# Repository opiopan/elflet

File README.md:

elflet
====

elflet is a home IoT controller based on [ESP-WROOM-32](https://www.espressif.com/en/products/hardware/modules) (ESP32). <br>
Both of hardware designe and firmware code are open source licenced. 
You are free to use any outcome from this project. And you are also free to modify hardware design and firmware code.<br>
elflet will join your home net work with WiFi.
Then elflet can controll home electronic devices through IR remote controll protocol or Bluetooth LE. 
And this device can be behave as sensor node such as temperature sensor.<br>
Unlike other similar products, elflet highly abstructs IR remote controll protocol. Therefore host-side software to collaborate with elflet is very easy to implement.

## Features

* **IR receiver**<br>
Receivd IR remote controller signal is analized such as following abstracted protocol data.

    ```json
    {
        "Protocol": "AEHA",
        "BitCount": 160,
        "Data": "11da270002000000000300001000000000000027"
    }
    ```
    Analized protocol data can be retrieved via 
    [REST interface](docs/REST.md), 
    or can be publishd via MQTT protocol.<br>
    **NOTE:** Supported protocols are NEC, SONY, and AEHA.

* **IR transmitter**<br> 
You can transmit IR remote controller signal by specifying the above level abstracted represatation.<br>
elflet supports two protocols for IR transmitter, 
The first one is 
[REST](docs/REST.md)
, and the other one is original binary protocol.
Regarding this binary protocol, please refer 
[these host-side library codes (`irslib.h`, `irslib.c`)](hosttool).

* **Device Shadow**<br>
Device shadow is designed to help complecated IR command device management such as air conditioner.<br>
elflet analize IR command code pattern according to registered shadow definition, then reflect device status to shadow representation managed in elflet. Following JSON data is a example of shadow status representation.
    ```json
    {
        "NodeName": "elflet-living", 
        "ShadowName": "ac",
        "IsOn": true,
        "Attributes":{
            "Mode": "Cooler",
            "Temperature": 26.5,
            "Humidity": 50
        }
    }
    ```

    Shadow status can be refered via 
    [REST interface](docs/REST.md), and status change of shadow device can be known immediately as publicshed data via MQTT.<br>
    You can also change shadow's status by sending the above format data to elflet via 
    [REST interface](docs/REST.md). 
    In this case, elflet synthesize IR code acording to shadow definition then transmit that.<br>
    A couple of shadow definition examples are shown at
    [here](examples).

* **BLE Keyboard Emulator**<br>
elflet can behave as Bluetooth LE (BLE) keyboard. You can send any key code to a device paired with elflet via Bluetooth LE.<br>
The typical use case of this function is to wake up a PC or server which does not accept WOL packet.

* **Environment Sensor**<br>
Following sensors are installed on elflet.
    * temperature sensor
    * humidity sensor
    * atmospheric pressure sensor
    * luminocity sensors

    You can retrieve sensor values via
    [REST interface](docs/REST.md),
    and can also receive them periodically as MQTT published message.<br>
    elflet supports a SENSOR-ONLY mode to avoid own heat affecting to measuring temperature. In this mode, elflet stays in deep sleep status except when sensor values is captured and they are published.
    You can transit elflet to SENSOR-ONLY mode by using
    [host tool](hosttool).

## PCB
PCB of elfet is designed by using [AUTODESK EAGLE](http://eagle.autodesk.com).
* PCB design files are placed [here](pcb/mainboard)
* You can also use [this gerver data](https://raw.githubusercontent.com/wiki/opiopan/elflet/pcb/elflet-mainboard.zip)
for production
* BOM list is [here](pcb/elflet-bom.xlsx?raw=true)

## Building Firmware
Firmware source codes are placed at 
[here](firmware).
To build firmware binary, please refer 
[this document](firmware/README.md).

## Inital Firmware Downloading
Once elflet firmware runs on elflet board, you can download firmware binary via WiFi (OTA updating). However, you need to download firmware via UART at first time since OTA updating function does not work yet.<br>
Folowing four binary files must be download at correct address in ESP-WROOM-32's SPI flash.

|file to download                        | adress  |
|:---------------------------------------|--------:|
| firmware/buld/bootloader/bootloader.bin|   0x1000|
| firmware/buld/partitions.bin           |   0x8000|
| firmware/build/ota_data_initial.bin    |   0xd000|
| firmware/buld/elflet.bin               |  0x10000|
| firmware/buld/spiffsimage.bin          | 0x3f0000|

elflet exports sevelal ESP32 pins to service port as below. You can download firmware by connection your USB serial dongle to there.

Another way to download firmware is using 
[this jig board](https://raw.githubusercontent.com/wiki/opiopan/elflet/pcb/elflet-jig.zip)
and Raspberry Pi. 
[These tools running on Raspberry Pi](raspitools)
may help you to download or debug elflet firmware.<br>
When use this jig board, please connect following direction.

## Configuration
When initial firmware downloading finish, LED on elflet starts to blink orange. In this state, elflet is working as WiFi access point and it provides Web based setup widzard interface.<br>
The SSID is same as node name of elflet, 
and the initial node name is "`elflet-000000`". Passphrase to connect elflet WiFi access point is same as administorator password, and the initial password is "`elflet00`".
Please connect to elflet WiFi access point by specifing these SSID and passphrase<br>

Once you connect to elflet WiFi access point, you can access to setup widzard. <br>
Since this wizard behaves as same mechanism of [captive portal](https://en.wikipedia.org/wiki/Captive_portal), typical OS shows that wizard window automatically when you connect to elflet WiFi access point.<br>
If no wizard window is shown, try a URL "```http://elflet.setup/```"

**NOTE:** Initial node name and initial administorator password can be change in step of building firmware. Please refer
[this document](firmware/README.md)
regarding the detail. 

By this wizard, you can configure following items:

* WiFi SSID and passphrase to connect
* elflet node name
* administorator password

When the wizard is completed, elflet restarts and LED start to blink white.
After that, elflet connect to your home network if configuration is correct, and LED turns off.<br>
If WiFi configuration is not correct and elflet cannot connect to your home network in 30 seconds, elflet will fall back to CONFIGURATION mode.
In this case, the LED start to blink orange again and you can access setup Wizard.

During elflet is connecting to your home network, setup widzard is not available. If you want to access setup wizard, please transit elflet to CONFIGURATION mode. You can proceed this transition by pressing a button till LED start to blink orange.

To change other detail configuration, please use a host tools, "`elflet-config`" and "`elflet-shadow`". Usage of these tools are described in [this document](hosttool/README.md).

## Licencing

elflet is released under dual open source licence.<br>
[The elfle firmware](firmware)
is in accordance with 
[GNU General Public License, version 2](https://www.gnu.org/licenses/old-licenses/gpl-2.0.en.html).
The other program source files, PCB design, and all documents are coverd by
[Apache License 2.0](http://www.apache.org/licenses/LICENSE-2.0).

## Application Example
My another project [Wakeserver](https://github.com/opiopan/wakeserver) is a good example of elfelt's application.

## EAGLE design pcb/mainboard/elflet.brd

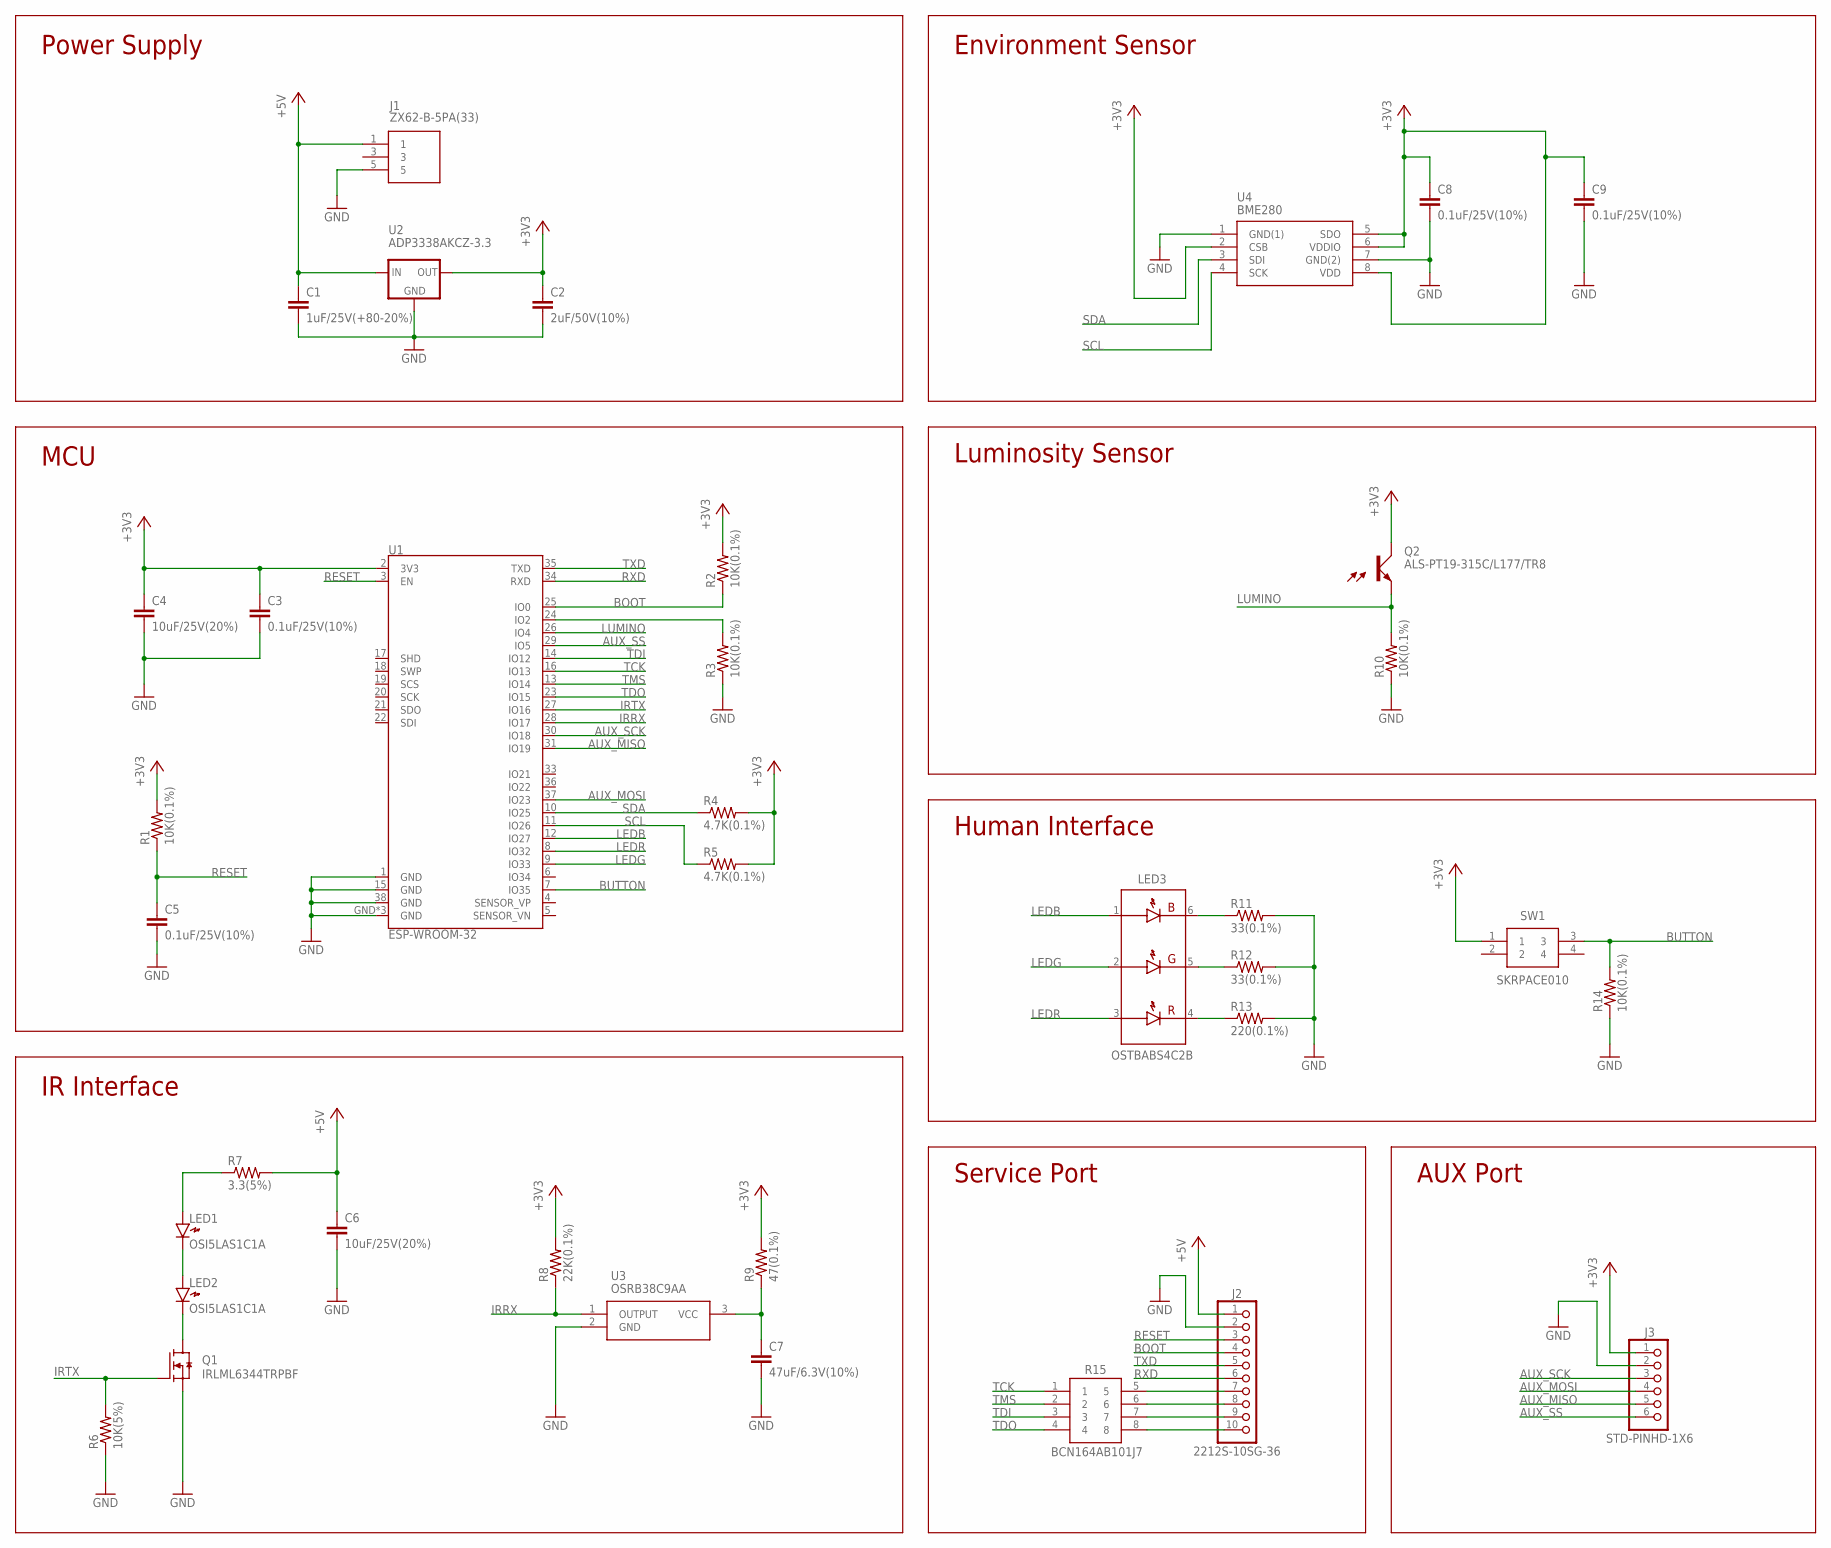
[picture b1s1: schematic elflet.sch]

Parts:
C1: 1uF/25V(+80-20%); C3216
C2: 2uF/50V(10%); C3216
C3, C5, C8, C9: 0.1uF/25V(10%); C1608
C4, C6: 10uF/25V(20%); C1608
C7: 47uF/6.3V(10%); C3216
J1: ZX62-B-5PA(33); ZX62-B-5PA(33)-TRUE-HANDSOLD
J2: 2212S-10SG-36; STD-1X10
J3: STD-PINHD-1X6; STD-1X6
LED1, LED2: OSI5LAS1C1A; PLCC-2
LED3: OSTBABS4C2B
Q1: IRLML6344TRPBF; SOT23
Q2: ALS-PT19-315C/L177/TR8; ALSPT19315CL177TR8
R1, R2, R3, R10, R14: 10K(0.1%); R0805
R4, R5: 4.7K(0.1%); R0603
R6: 10K(5%); R0805
R7: 3.3(5%); R2512
R8: 22K(0.1%); R0603
R9: 47(0.1%); R0603
R11, R12: 33(0.1%); R0805
R13: 220(0.1%); R0805
R15: BCN164AB101J7; BCN164A_1
SW1: SKRPACE010; SMT(4.2X3.2)
U1: ESP-WROOM-32; ESP-WROOM-03
U2: ADP3338AKCZ-3.3; SOT223
U3: OSRB38C9AA; OSRB38C9AA-ALT
U4: BME280

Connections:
+3V3: C2.1, C3.1, C4.1, C8.1, C9.1, J3.1, Q2.1 (C), R1.2, R2.2, R4.2, R5.2, R8.2, R9.2, SW1.1, U1.2 (3V3), U2.2 (OUT), U2.4 (OUT), U4.2 (CSB), U4.5 (SDO), U4.6 (VDDIO), U4.8 (VDD)
+5V: C1.1, C6.1, J1.1, J2.1, R7.2, U2.3 (IN)
AUX_MISO: J3.5, U1.31 (IO19)
AUX_MOSI: J3.4, U1.37 (IO23)
AUX_SCK: J3.3, U1.30 (IO18)
AUX_SS: J3.6, U1.29 (IO5)
BOOT: J2.4, R2.1, U1.25 (IO0)
BUTTON: R14.2, SW1.3, U1.7 (IO35)
GND: C1.2, C2.2, C3.2, C4.2, C5.2, C6.2, C7.2, C8.2, C9.2, J1.5, J2.2, J3.2, Q1.2 (S), R3.1, R6.1, R10.1, R11.2, R12.2, R13.2, R14.1, U1.1 (GND), U1.15 (GND), U1.38 (GND), U1.GND, U1.GND_B (GND), U1.GND_V (GND), U2.1 (GND), U3.2 (GND), U4.1 (GND(1)), U4.7 (GND(2))
IRRX: R8.1, U1.28 (IO17), U3.1 (OUTPUT)
IRTX: Q1.1 (G), R6.2, U1.27 (IO16)
LEDB: LED3.1 (AB), U1.12 (IO27)
LEDG: LED3.2 (AG), U1.9 (IO33)
LEDR: LED3.3 (AR), U1.8 (IO32)
LUMINO: Q2.2 (E), R10.2, U1.26 (IO4)
unnamed: R3.2, U1.24 (IO2)
unnamed: LED1.1 (K), LED2.2 (A)
unnamed: LED2.1 (K), Q1.3 (D)
unnamed: LED1.2 (A), R7.1
unnamed: C7.1, R9.1, U3.3 (VCC)
unnamed: J2.7, R15.5
unnamed: J2.8, R15.6
unnamed: J2.9, R15.7
unnamed: LED3.6 (KB), R11.1
unnamed: LED3.5 (KG), R12.1
unnamed: LED3.4 (KR), R13.1
unnamed: J2.10, R15.8
RESET: C5.1, J2.3, R1.1, U1.3 (EN)
RXD: J2.6, U1.34 (RXD)
SCL: R5.1, U1.11 (IO26), U4.4 (SCK)
SDA: R4.1, U1.10 (IO25), U4.3 (SDI)
TCK: R15.1, U1.16 (IO13)
TDI: R15.3, U1.14 (IO12)
TDO: R15.4, U1.23 (IO15)
TMS: R15.2, U1.13 (IO14)
TXD: J2.5, U1.35 (TXD)

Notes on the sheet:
MCU
Power Supply
IR Interface
Environment Sensor
Luminosity Sensor
Human Interface
Service Port
AUX Port

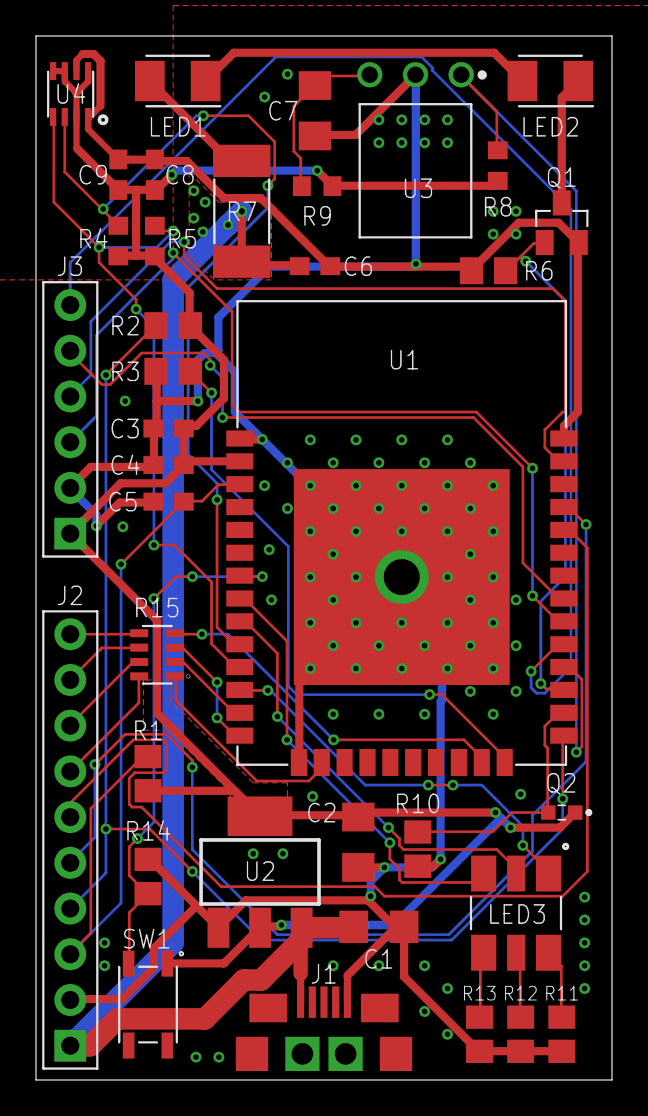
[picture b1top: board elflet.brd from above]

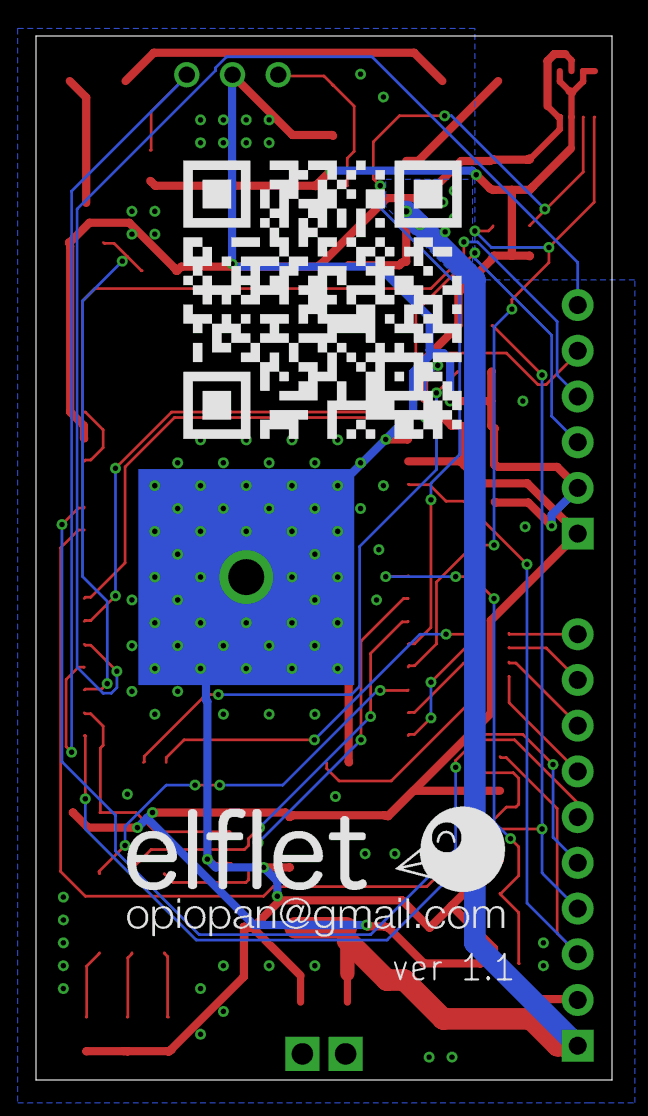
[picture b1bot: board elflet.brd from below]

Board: 2 copper layers, 32.0 x 58.0 mm, 39 parts (2 on the bottom side), 36 nets.

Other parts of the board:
U$1: ELFLET-LOGO
U$2: ELFLET-QRCODE

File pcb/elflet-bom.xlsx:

elflet main board BOM
Label | Attribute | Product id | Quantity | Recommended Seller | URL
U1 | ESP32 module | ESP-WROOM-32 | 1 | Akizuki | http://akizukidenshi.com/catalog/g/gM-11647/
U2 | 3,3V 1A LDO | ﻿ADP3338AKCZ-3.3 | 1 |  | http://akizukidenshi.com/catalog/g/gI-12635/
U3 | IR reciever module | ﻿OSRB38C9AA | 1 |  | http://akizukidenshi.com/catalog/g/gI-04659/
U4 | Environment sensor | BME280 | 1 | AliExpress | https://www.aliexpress.com/wholesale?SearchText=BME280+chip
Q1 | Nch MOS-FET | ﻿IRLML6344TRPBF | 1 | Akizuki | http://akizukidenshi.com/catalog/g/gI-06049/
Q2 | Photo transistor | ﻿ALS-PT19-315C/L177/TR8 | 1 | Marutsu | https://www.marutsu.co.jp/GoodsListNavi.jsp?path=&q=ALS-PT19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
LED1, LED2 | PLCC-2/IR LED | ﻿OSI5LAS1C1A | 2 | Akizuki | http://akizukidenshi.com/catalog/g/gI-06427/
LED3 | PLCC-6/Full Color LED | ﻿OSTBABS4C2B | 1 |  | http://akizukidenshi.com/catalog/g/gI-06117/
J1 | Micro USB female connector | ﻿ZX62-B-5PA(33) | 1 |  | http://akizukidenshi.com/catalog/g/gC-11183/
J2 | low hight pin socket | 2212S-10G-36 | 1 |  | http://akizukidenshi.com/catalog/g/gC-03138/
J3 | NC | - | - | -
SW1 | SMD tact switch | ﻿SKRPACE010 | 1 | Akizuki | http://akizukidenshi.com/catalog/g/gP-06185/
C1 | 3216/1uF/25V(+80-20%) | ECJ(L(3))FF1E105Z | 1 |  | http://akizukidenshi.com/catalog/g/gP-08708/
C2 | 3216/4.7uF/16V(+80-20%) | GRM31MF11C475ZA01 | 1 |  | http://akizukidenshi.com/catalog/g/gP-04661/
C3, C5, C8, C9 | 1608/﻿0.1uF/25V(10%) | GRM188B11E104KA01 | 4 |  | http://akizukidenshi.com/catalog/g/gP-05616/
C4, C6 | 1608/﻿10uF/25V(20%) | GRM188R61E106MA | 2 |  | http://akizukidenshi.com/catalog/g/gP-07768/
C7 | 3216/﻿47uF/6.3V(10%) | GRM31CB30J476ME18 | 1 |  | http://akizukidenshi.com/catalog/g/gP-02058/
R1, R2, R3, R6, R10, R14 | 2012/﻿10K/0.1W(0.1%) | AR05BTC1002 | 6 | Sengoku | https://www.sengoku.co.jp/mod/sgk_cart/detail.php?code=EEHD-0HUG
R4, R5 | 1608/﻿4.7K/0.063W/(0.1%) | AR03BTC4701 | 2 |  | https://www.sengoku.co.jp/mod/sgk_cart/detail.php?code=EEHD-0GXT
R7 | ﻿6331/3.3/1W(5%) | RK73BW3ATTE3R3J | 1 |  | https://www.sengoku.co.jp/mod/sgk_cart/detail.php?code=EEHD-0ETM
R8 | 1608/﻿22K/0.063W(0.1%) | AR03BTC2202 | 1 |  | https://www.sengoku.co.jp/mod/sgk_cart/detail.php?code=EEHD-0GYD
R9 | 1608/47/0.063W(0.1%) | AR03BTC0470 | 1 |  | https://www.sengoku.co.jp/mod/sgk_cart/detail.php?code=EEHD-0GW7
R11, R12 | 2012/﻿33/0.1W(0.1%) | AR05BTC0330 | 2 |  | https://www.sengoku.co.jp/mod/sgk_cart/detail.php?code=EEHD-0HSF
R13 | 2012/﻿220/0,1W(0.1%) | AR05BTC2200 | 1 |  | https://www.sengoku.co.jp/mod/sgk_cart/detail.php?code=EEHD-0HT5
R15 | Array 100/0.063W(5%) | ﻿BCN164AB101J7 | 1 |  | https://www.sengoku.co.jp/mod/sgk_cart/detail.php?code=6AXT-E7J2
elflet jig BOM
Label | Attribute | Product id | Quantity | Recommended Seller | URL
 | low height pin connector | PH-1x40SG/9.54 | 1 | Akizuki | http://akizukidenshi.com/catalog/g/gC-00171/
 | L type narrow 10 pin header | PHA-1x10RG | 2 |  | http://akizukidenshi.com/catalog/g/gC-06362/
 | 2x20 female pin socket | 2214S-40G-85 | 1 |  | http://akizukidenshi.com/catalog/g/gC-09717/
 | 10 pin female dupont cable | - | 1 | DIY or AliExpress

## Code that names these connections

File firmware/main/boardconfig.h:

#pragma once

#include "version.h"

#define GPIO_BUTTON   35
#define GPIO_LEDR     32
#define GPIO_LEDG     33
#define GPIO_LEDB     27
#define GPIO_IRLED    16
#define GPIO_IRRX     17
#define GPIO_I2C_SDA  25
#define GPIO_I2C_SCL  26
#define GPIO_LUMINO   4
#define GPIO_AUX_SCK  18
#define GPIO_AUX_MISO 19
#define GPIO_AUX_MOSI 23
#define GPIO_AUX_SS   5

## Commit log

2018-04-19 place all parts on a board
2018-04-22 initial wiring
2018-04-22 add jig board pcb design
2018-04-23 add logo silk
2018-04-29 optimized for panerizing
2018-04-29 add panelize script
2018-05-01 improved data & tools for panelizing
2018-05-03 improve panelizing
2018-05-08 rewiring
2018-05-13 fix usb connector issue
2018-05-27 add firmware code base
2018-05-27 add json11 as submodule
2018-05-29 add configuration persisitence feature
2018-05-31 add WiFi AP mode in factory reset status and configuration status, adn add OTA update feature
2018-06-01 add ir transmitter, STA mode, and configuration REST
2018-06-03 implement LED indicator feature
2018-06-03 supported button interface
2018-06-04 fix button bug
2018-06-04 change irserver protocol
2018-06-06 add IR reciever capability
2018-06-06 add retrieve RAW IR sequence data function
2018-06-06 fix a LED fade bug
2018-06-08 add a feature that IR command can be sent via REST interface
2018-06-10 add a feature which can be retrieve sensor values via REST
2018-06-10 improve sensor capturering function to detect if bme280 is installed or not
2018-06-10 add tools to use in raspberry pi environment
2018-06-11 prepare to imprement Web UI
2018-06-11 fix large http body response problem
2018-06-16 start to implement setup wizard
2018-06-17 add setup wizard function
2018-06-18 improve wizard UI
2018-06-20 support compressed http response
2018-06-20 rename a part of web related files
2018-06-20 minor update
2018-06-21 change wizard color
2018-06-23 minor updating
2018-06-25 correnspond to latest esp-idf and prepare to implement mqtt publish function
2018-06-26 add configuration parameters to support mqtt publishing function
2018-06-26 fix raspi-tool issue
2018-06-27 add publish sensor value function
2018-06-27 fix publishing bug
2018-06-28 prepare to generalize publish function as Pub/Sub function
2018-06-30 add publishing IRC recieved data feature
2018-07-01 add Sensor-Only mode which works in deep sleep status except publishing sensor data
2018-07-02 improve stability of mqtt connection and publishing
2018-07-04 add resolving mDNS host name function
2018-07-08 refactoring
2018-07-08 auto genarating firmware version
2018-07-09 enable to specify ntp server
2018-07-09 reduce cpu consumption during connecting WiFi
2018-07-12 minor bug fix
2018-07-15 fix a problem that retained message could not be recieved
2018-07-21 prepare to implement a downloading firmware when mqtt message issued
2018-07-24 add OTA update capability issued via mqtt
2018-07-24 fix minor bug
2018-07-28 fix a bug that long IR comand could not be sent
2018-08-01 add new IR reciever mode which works continuously
2018-08-15 fix a continuous ir recieving bug
2018-08-18 add device shadow function
2018-08-19 allow to register a shadow definition not containing a shadow name
2018-08-19 change interpretation of zero lenght pub/sub topic name
2018-08-22 prepare to add user defined attribute to shadow
2018-08-26 add user defined attribute to device shadow
2018-08-28 fix issues related user defined attribute in device shadow and optimize stack size of each task
2018-08-28 fix a problem that retrying to connect to MQTT broaker never succeed in case of the broaker does not work when elflet boot
2018-08-28 add REST I/F to get status
2018-08-29 add a function to publish shadow status
2018-08-30 fix a bug that topic name for shadow status could not be changed
2018-09-01 add collecting statistics function
2018-09-02 prepare to imprement synthesizing function for device shadow
2018-09-04 add IR command synthesizing capability to device shadow
2018-09-05 fix a bug of monadic operator for synthesizer variable
2018-09-05 fix statistics bug
2018-09-06 fix minor issue
2018-09-08 fix a issue that changing mode by holding button will fail
2018-09-08 add statistics information
2018-10-21 improve PCB design to support fusion360 relation
2018-11-03 fix a issue of shows status serialization
2018-11-19 enable to change WiFi country code
2018-12-19 update for 3d model
2018-12-22 add Bluetooth Keyboard (BLE keyboard) emulation to wake up a computer from sleep state
2018-12-23 update some log messages
2018-12-24 add a configuration CLI tool
2018-12-24 fix a minor issue
2018-12-24 fix a minor bug
2018-12-24 add a CLI to manage shadow
2018-12-24 fix hosttool installer bug
2018-12-25 sophisticate build environment
2018-12-25 improve reliability in sensor only mode
2018-12-26 improve accuracy of RTC in SensorOnly mode
2018-12-29 shadow status persistense capability is added
2018-12-31 add shadow definition samples
2019-01-01 can recieve over 200 bit command
2019-01-04 sophisticate build system
2019-01-04 fix IRRC REST problem
2019-01-04 fix elflet.json issue
2019-01-06 add README.md
2019-01-07 improve reliability while enabling BLE
2019-01-07 Create LICENSE
2019-01-07 Update LICENSE
2019-01-07 update licence, and add building firmware procedure
2019-01-08 change README of build procedure
2019-01-09 add REST specification
2019-01-09 add description of host tools
2019-01-12 correct spelling
2019-02-02 add configuration filese for Visual Studio Code
2019-02-02 replace tab code as space
2019-02-03 fix minor bugs of host-tools and raspi-tools
2019-02-03 change submodule folder names
2019-02-03 fix a mislink in README.md
2019-02-03 improve debug environment on Raspberry Pi
2019-04-21 add shadow examples
2019-04-22 auto reconnect to WiFi after fall backing to Configuration Mode, close #1
2019-12-07 update degug configuration
2020-01-03 fix an issue that HTTP keep-alive cannot handle correctly
2020-01-04 fix a issue that 100% of CPU cycle is consumed in setup mode
2020-01-12 changed setup wizard that behaves as captive portal
2020-01-13 improved captive portal behavior in setup mode
2020-01-31 changed esp-dns-hijack-srv submodule from my forked version to original version
2020-04-30 prepare to support a function that send BLE HID code by pressing a button
2020-05-03 add a function sending HID code via BLE when button on elflet is pressed
2020-05-04 tuned timing of initalizing each device
2020-05-05 complient to ESP-IDF 3.3.2
2020-05-07 allow to disable WiFi connectivity if BLE keyboard function is working
2020-05-07 improve logging
2020-05-10 compatible with ESP-IDF 4.0
2020-05-17 rewrited BLE keyboard emulation code based on new exsample code using esp-hid component
2020-07-01 update scripts for Raspberry Pi
2023-10-28 hosttools are now adapted to Python3
2023-10-28 fixed a minor issue regarding Makefile for hosttool
2023-11-03 adapted to ESP-IDF 4.1
2023-11-03 improved expressive abillity of shadow definition
2023-11-07 updated firmware building procedure
2025-05-03 changed a debugging script to adapt to OpenOCD 0.12.0
2025-05-06 Preparation for migrating the build system from GNU Make to CMake
2025-05-07 removed an unused submodule
2025-05-17 adapted to CMake buildtools but some convenience targets are not supported
2025-05-18 addressed an oversight where some changes were not committed
2025-05-18 addressed an issue in CMake where updating embedded version information in the binary may not work correctly
2025-06-01 Improved the expressiveness of the Device Shadow
2025-06-01 Added an shadow definition example for panasonic AC
2025-06-06 Added support for generating multi-frame IR command
2025-06-07 Changed the IR command transmission function from asynchronous to synchronous operation
2025-06-07 Enabled embedding date and time as values during IR command synthesis
2025-06-07 Improved accuracy of the frame interval for the device shadow IR command synthesising
2025-06-08 Improved the expressiveness of the device shadow definition: It is now possible to specify conditional expressions—equivalent to those used during IR command interpretation—as activation conditions f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
2025-06-08 Updated a shadow example for the Panasonic AC
